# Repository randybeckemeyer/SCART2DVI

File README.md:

# SCART2DVI
SCART to DVI converter ideal for video capture

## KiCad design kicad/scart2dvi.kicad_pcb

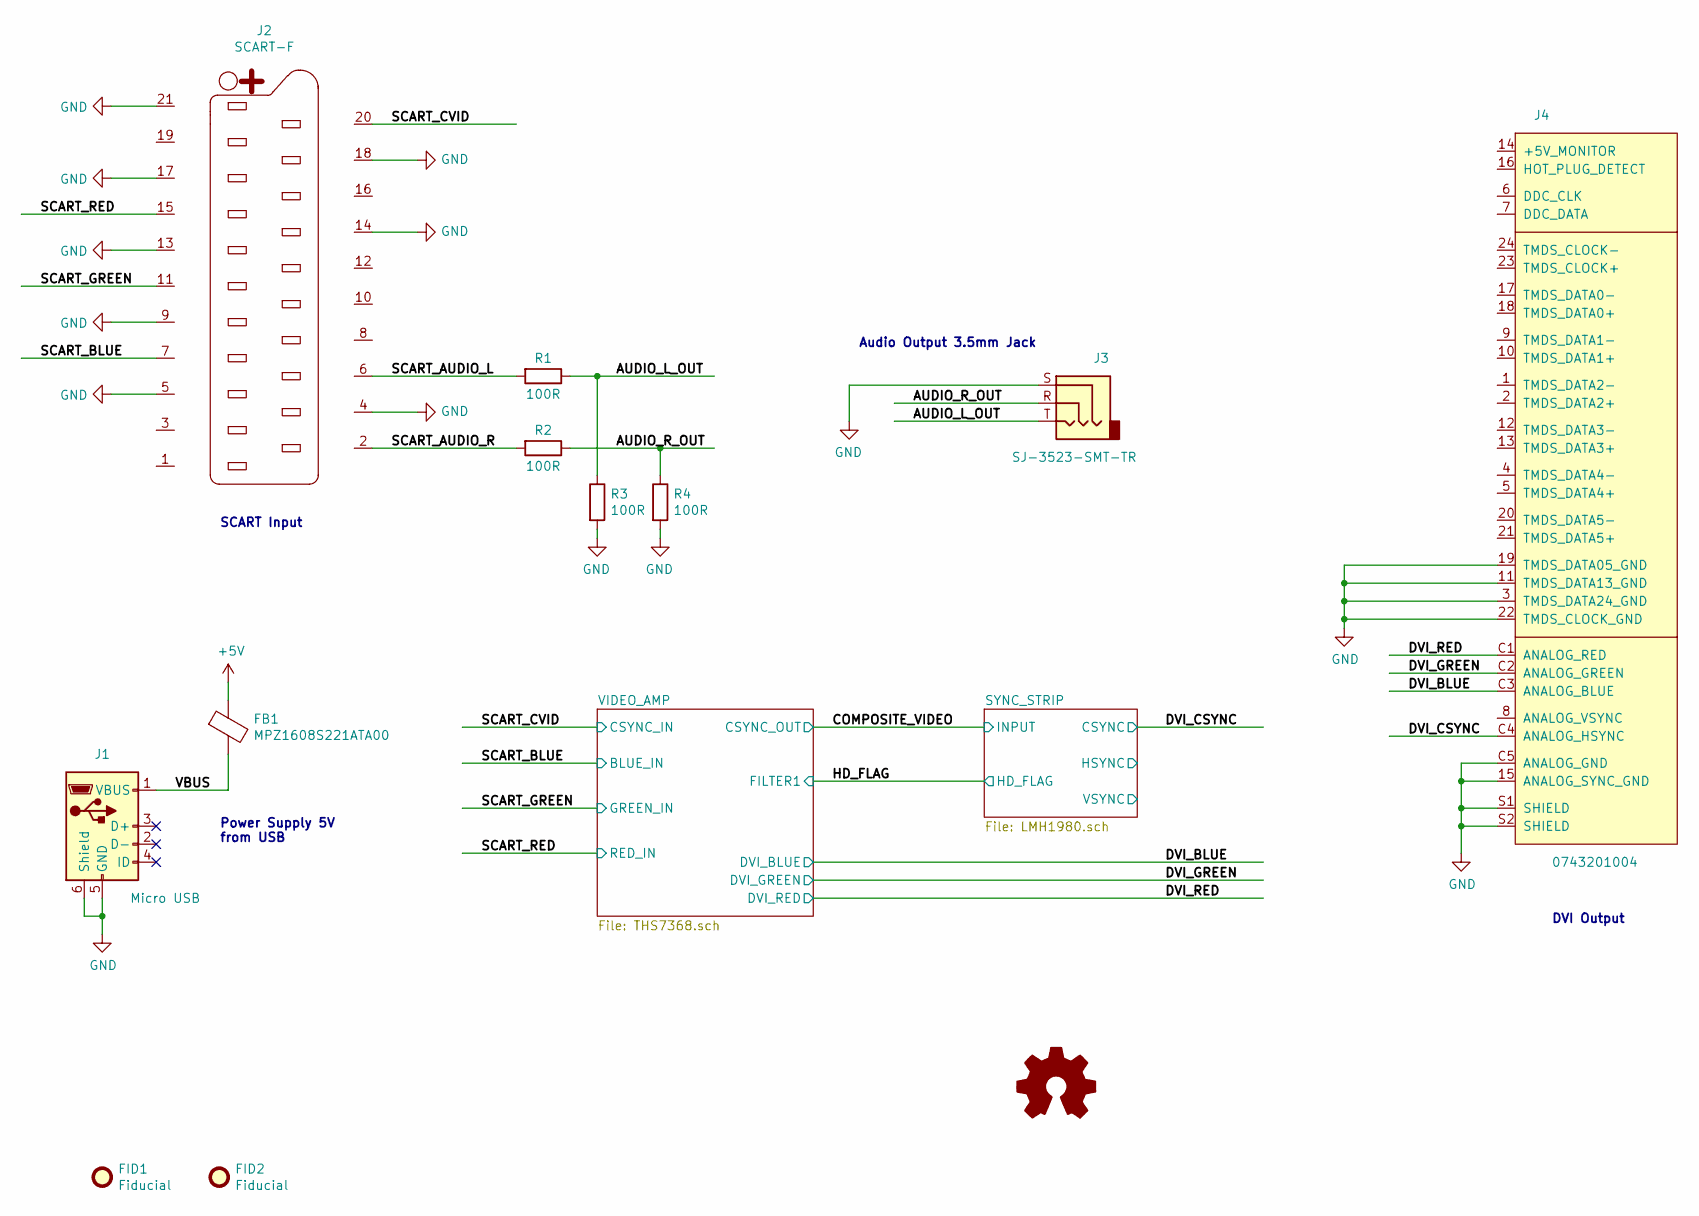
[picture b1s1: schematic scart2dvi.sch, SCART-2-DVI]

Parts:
FB1: MPZ1608S221ATA00; L_0603_1608Metric_Pad1.05x0.95mm_HandSolder; MPN MPZ1608S221ATA00; Digikey 445-1565-1-ND
FID1, FID2: Fiducial; Fiducial_1mm_Mask2mm
J1: Micro USB; USB_Micro-B_Molex-105017-0001; MPN 1050170001; Digikey WM1399CT-ND
J2: SCART-F; SCART-CS-107
J3: SJ-3523-SMT-TR; Jack_3.5mm_CUI_SJ-3523-SMT_Horizontal; MPN SJ-3523-SMT-TR; Digikey CP-3523SJCT-ND
J4: 0743201004; Connector-DVI-0743201004; Digikey WM5600-ND
LOGO1: Logo_Open_Hardware_Small; OSHW-Logo2_14.6x12mm_SilkScreen
R1, R2, R3, R4: 100R; R_0603_1608Metric_Pad1.05x0.95mm_HandSolder; MPN RC0603FR-07100RL; Digikey 311-100HRCT-ND

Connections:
+5V: FB1.1; also elsewhere on the board
/AUDIO_L_OUT: J3.T, R1.1, R3.1
/AUDIO_R_OUT: J3.R, R2.1, R4.1
/DVI_BLUE: J4.C3 (ANALOG_BLUE); also elsewhere on the board
/DVI_CSYNC: J4.C4 (ANALOG_HSYNC); also elsewhere on the board
/DVI_GREEN: J4.C2 (ANALOG_GREEN); also elsewhere on the board
/DVI_RED: J4.C1 (ANALOG_RED); also elsewhere on the board
/SCART_AUDIO_L: J2.6, R1.2
/SCART_AUDIO_R: J2.2, R2.2
/SCART_BLUE: J2.7; also elsewhere on the board
/SCART_CVID: J2.20; also elsewhere on the board
/SCART_GREEN: J2.11; also elsewhere on the board
/SCART_RED: J2.15; also elsewhere on the board
/VBUS: FB1.2, J1.1 (VBUS)
GND: J1.5 (GND), J1.6 (Shield), J2.4, J2.5, J2.9, J2.13, J2.14, J2.17, J2.18, J2.21, J3.S, J4.3 (TMDS_DATA24_GND), J4.11 (TMDS_DATA13_GND), J4.15 (ANALOG_SYNC_GND), J4.19 (TMDS_DATA05_GND), J4.22 (TMDS_CLOCK_GND), J4.C5 (ANALOG_GND), J4.S1 (SHIELD), J4.S2 (SHIELD), R3.2, R4.2; also elsewhere on the board

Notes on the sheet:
Power Supply 5V from USB
Audio Output 3.5mm Jack
DVI Output
SCART Input

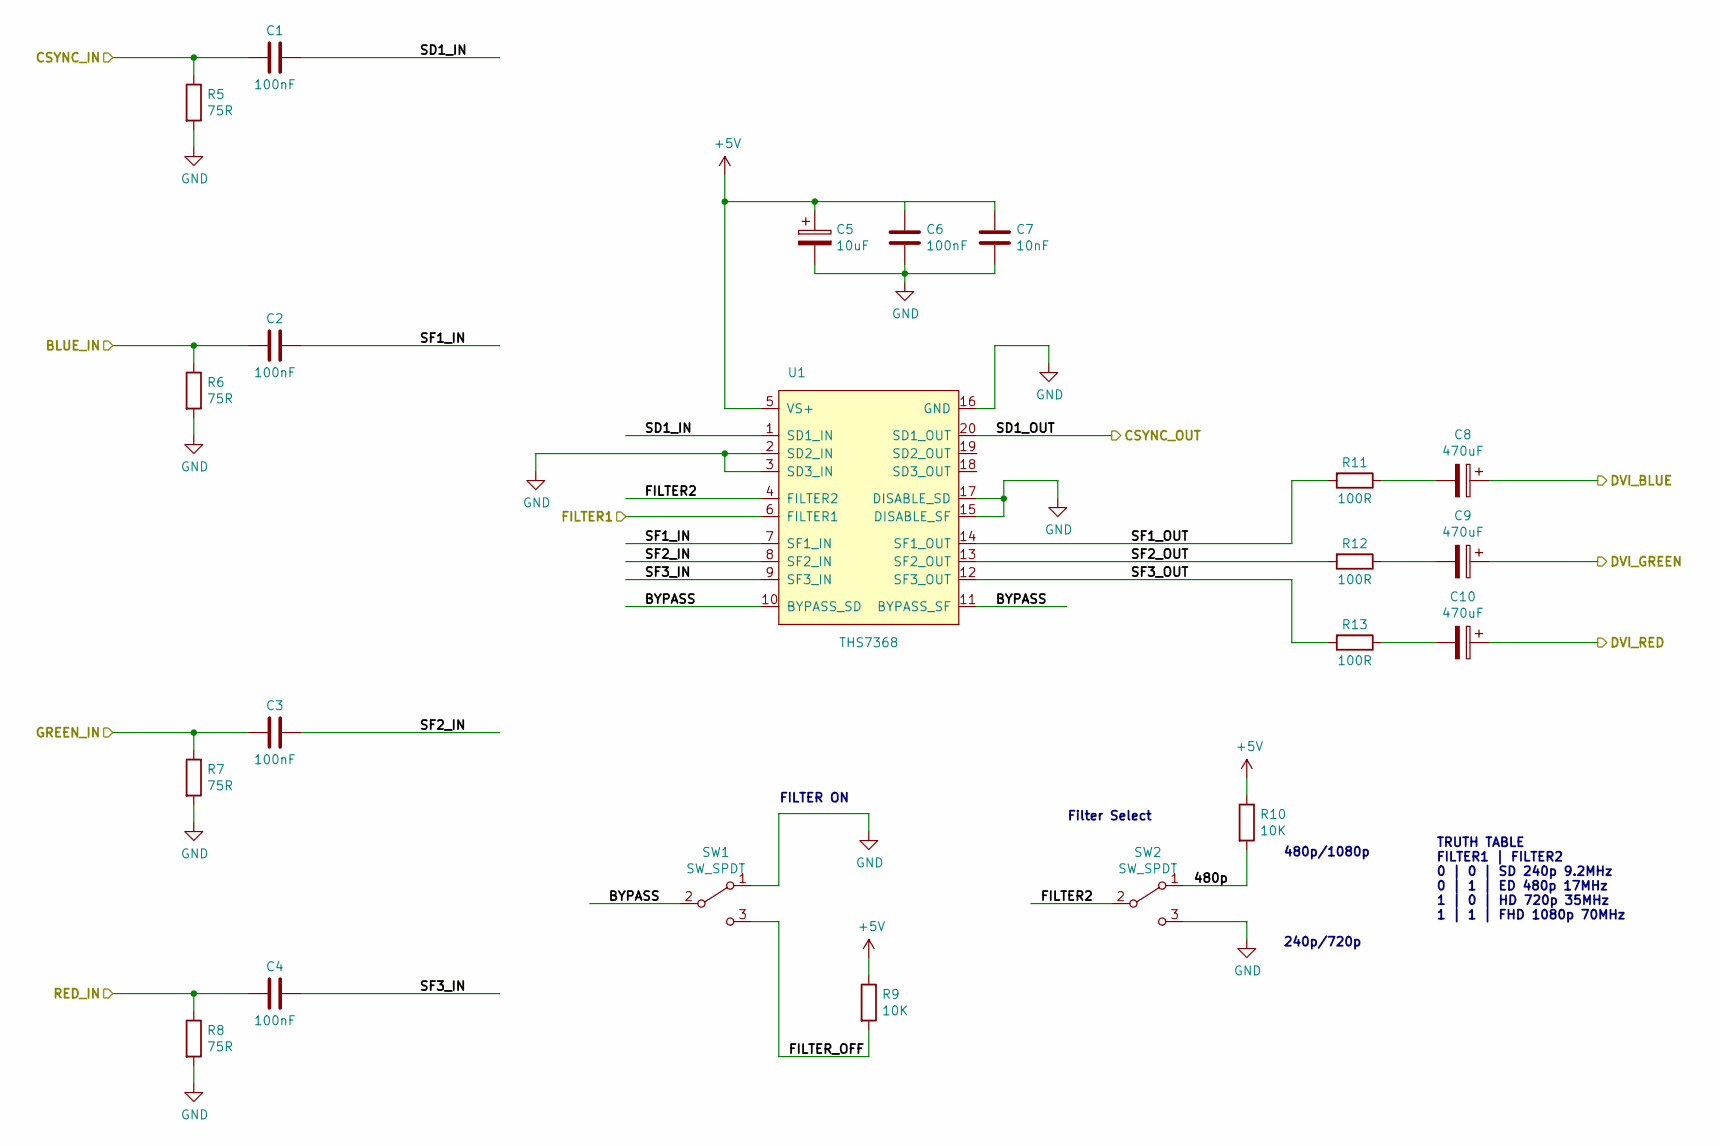
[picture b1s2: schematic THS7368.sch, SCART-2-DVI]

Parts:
C1, C2, C3, C4, C6: 100nF; C_0603_1608Metric_Pad1.05x0.95mm_HandSolder; MPN CC0603KRX7R9BB104; Digikey 311-1344-1-ND
C5: 10uF; CP_EIA-3216-18_Kemet-A_Pad1.58x1.35mm_HandSolder; MPN TAJA106K016RNJ; Digikey 478-1655-1-ND
C7: 10nF; C_0603_1608Metric_Pad1.05x0.95mm_HandSolder; MPN CC0603KRX7R9BB103; Digikey 311-1085-1-ND
C8, C9, C10: 470uF; CP_Elec_8x10.5; MPN EEE-HA1A471UP; Digikey PCE4178CT-ND
R5, R6, R7, R8: 75R; R_0603_1608Metric_Pad1.05x0.95mm_HandSolder; MPN RC0603FR-0775RL; Digikey 311-75.0HRCT-ND
R9, R10: 10K; R_0603_1608Metric_Pad1.05x0.95mm_HandSolder; MPN RC0603FR-0710KL; Digikey 311-10.0KHRCT-ND
R11, R12, R13: 100R; R_0603_1608Metric_Pad1.05x0.95mm_HandSolder; MPN RC0603FR-07100RL; Digikey 311-100HRCT-ND
SW1, SW2: SW_SPDT; SW_NKK_GW12RCV; MPN GW12RCV; Digikey 360-3430-ND
U1: THS7368; TSSOP-20_4.4x6.5mm_P0.65mm; MPN THS7368IPWR; Digikey 296-25625-1-ND

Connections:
+5V: C5.1, C6.1, C7.1, R9.1, R10.1, U1.5 (VS+); also elsewhere on the board
/COMPOSITE_VIDEO: U1.20 (SD1_OUT); also elsewhere on the board
/DVI_BLUE: C8.1; also elsewhere on the board
/DVI_GREEN: C9.1; also elsewhere on the board
/DVI_RED: C10.1; also elsewhere on the board
/HD_FLAG: U1.6 (FILTER1); also elsewhere on the board
/SCART_BLUE: C2.2, R6.1; also elsewhere on the board
/SCART_CVID: C1.2, R5.1; also elsewhere on the board
/SCART_GREEN: C3.2, R7.1; also elsewhere on the board
/SCART_RED: C4.2, R8.1; also elsewhere on the board
/VIDEO_AMP/480p: R10.2, SW2.1 (A)
/VIDEO_AMP/BYPASS: SW1.2 (B), U1.10 (BYPASS_SD), U1.11 (BYPASS_SF)
/VIDEO_AMP/FILTER2: SW2.2 (B), U1.4 (FILTER2)
/VIDEO_AMP/FILTER_OFF: R9.2, SW1.3 (C)
/VIDEO_AMP/SD1_IN: C1.1, U1.1 (SD1_IN)
/VIDEO_AMP/SF1_IN: C2.1, U1.7 (SF1_IN)
/VIDEO_AMP/SF1_OUT: R11.2, U1.14 (SF1_OUT)
/VIDEO_AMP/SF2_IN: C3.1, U1.8 (SF2_IN)
/VIDEO_AMP/SF2_OUT: R12.2, U1.13 (SF2_OUT)
/VIDEO_AMP/SF3_IN: C4.1, U1.9 (SF3_IN)
/VIDEO_AMP/SF3_OUT: R13.2, U1.12 (SF3_OUT)
GND: C5.2, C6.2, C7.2, R5.2, R6.2, R7.2, R8.2, SW1.1 (A), SW2.3 (C), U1.2 (SD2_IN), U1.3 (SD3_IN), U1.15 (DISABLE_SF), U1.16 (GND), U1.17 (DISABLE_SD); also elsewhere on the board
unnamed: C8.2, R11.1
unnamed: C9.2, R12.1
unnamed: C10.2, R13.1

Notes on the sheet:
FILTER ON
TRUTH TABLE FILTER1 | FILTER2 0 | 0 | SD 240p 9.2MHz 0 | 1 | ED 480p 17MHz 1 | 0 | HD 720p 35MHz 1 | 1 | FHD 1080p 70MHz
Filter Select
240p/720p
480p/1080p

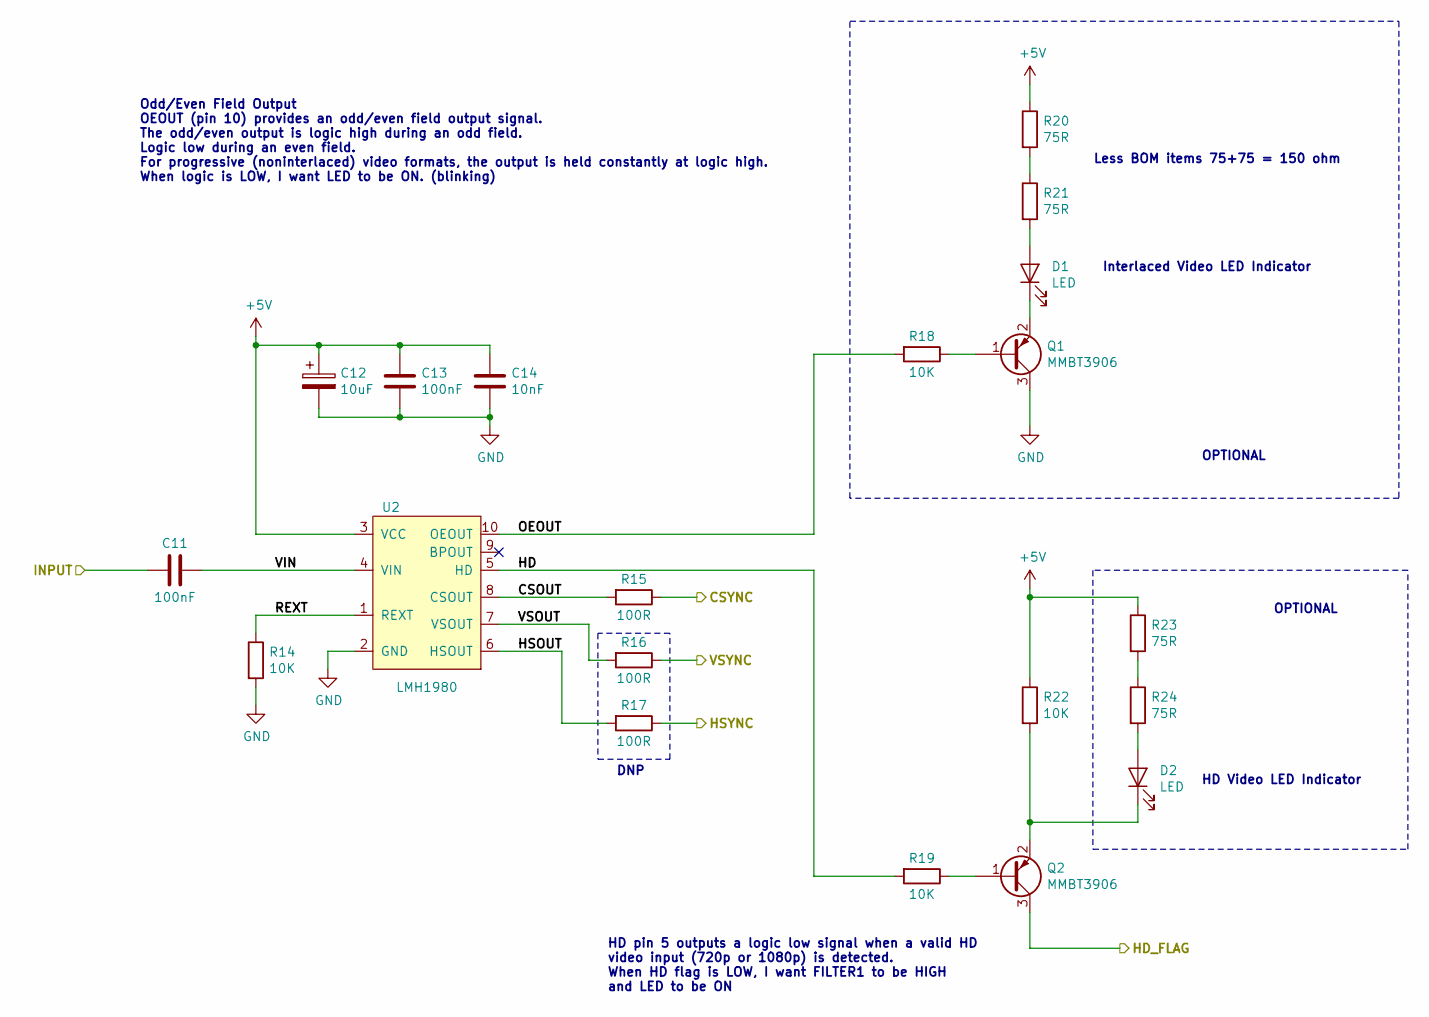
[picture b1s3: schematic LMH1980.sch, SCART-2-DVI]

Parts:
C11, C13: 100nF; C_0603_1608Metric_Pad1.05x0.95mm_HandSolder; MPN CC0603KRX7R9BB104; Digikey 311-1344-1-ND
C12: 10uF; CP_EIA-3216-18_Kemet-A_Pad1.58x1.35mm_HandSolder; MPN TAJA106K016RNJ; Digikey 478-1655-1-ND
C14: 10nF; C_0603_1608Metric_Pad1.05x0.95mm_HandSolder; MPN CC0603KRX7R9BB103; Digikey 311-1085-1-ND
D1, D2: LED; LED_0603_1608Metric_Pad1.05x0.95mm_HandSolder; MPN LTST-C190GKT; Digikey 160-1183-1-ND
Q1, Q2: MMBT3906; SOT-23; MPN MMBT3906LT1G; Digikey MMBT3906LT1GOSCT-ND
R14, R18, R19, R22: 10K; R_0603_1608Metric_Pad1.05x0.95mm_HandSolder; MPN RC0603FR-0710KL; Digikey 311-10.0KHRCT-ND
R15, R16, R17: 100R; R_0603_1608Metric_Pad1.05x0.95mm_HandSolder; MPN RC0603FR-07100RL; Digikey 311-100HRCT-ND
R20, R21, R23, R24: 75R; R_0603_1608Metric_Pad1.05x0.95mm_HandSolder; MPN RC0603FR-0775RL; Digikey 311-75.0HRCT-ND
U2: LMH1980; TSSOP-10_3x3mm_P0.5mm; MPN LMH1980MM/NOPB; Digikey LMH1980MM/NOPBCT-ND

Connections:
+5V: C12.1, C13.1, C14.1, R20.1, R22.1, R23.1, U2.3 (VCC); also elsewhere on the board
/COMPOSITE_VIDEO: C11.2; also elsewhere on the board
/DVI_CSYNC: R15.1; also elsewhere on the board
/HD_FLAG: Q2.3 (C); also elsewhere on the board
/SYNC_STRIP/CSOUT: R15.2, U2.8 (CSOUT)
/SYNC_STRIP/HD: R19.2, U2.5 (HD)
/SYNC_STRIP/HSOUT: R17.2, U2.6 (HSOUT)
/SYNC_STRIP/HSYNC: R17.1
/SYNC_STRIP/OEOUT: R18.2, U2.10 (OEOUT)
/SYNC_STRIP/REXT: R14.1, U2.1 (REXT)
/SYNC_STRIP/VIN: C11.1, U2.4 (VIN)
/SYNC_STRIP/VSOUT: R16.2, U2.7 (VSOUT)
/SYNC_STRIP/VSYNC: R16.1
GND: C12.2, C13.2, C14.2, Q1.3 (C), R14.2, U2.2 (GND); also elsewhere on the board
unnamed: D1.1 (K), Q1.2 (E)
unnamed: D1.2 (A), R21.2
unnamed: D2.1 (K), Q2.2 (E), R22.2
unnamed: D2.2 (A), R24.2
unnamed: Q1.1 (B), R18.1
unnamed: Q2.1 (B), R19.1
unnamed: R20.2, R21.1
unnamed: R23.2, R24.1

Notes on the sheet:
HD pin 5 outputs a logic low signal when a valid HD video input (720p or 1080p) is detected. When HD flag is LOW, I want FILTER1 to be HIGH and LED to be ON
Odd/Even Field Output OEOUT (pin 10) provides an odd/even field output signal. The odd/even output is logic high during an odd field. Logic low during an even field. For progressive (noninterlaced) video formats, the output is held constantly at logic high. When logic is LOW, I want LED to be ON. (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
Interlaced Video LED Indicator
HD Video LED Indicator
Less BOM items 75+75 = 150 ohm
DNP
OPTIONAL

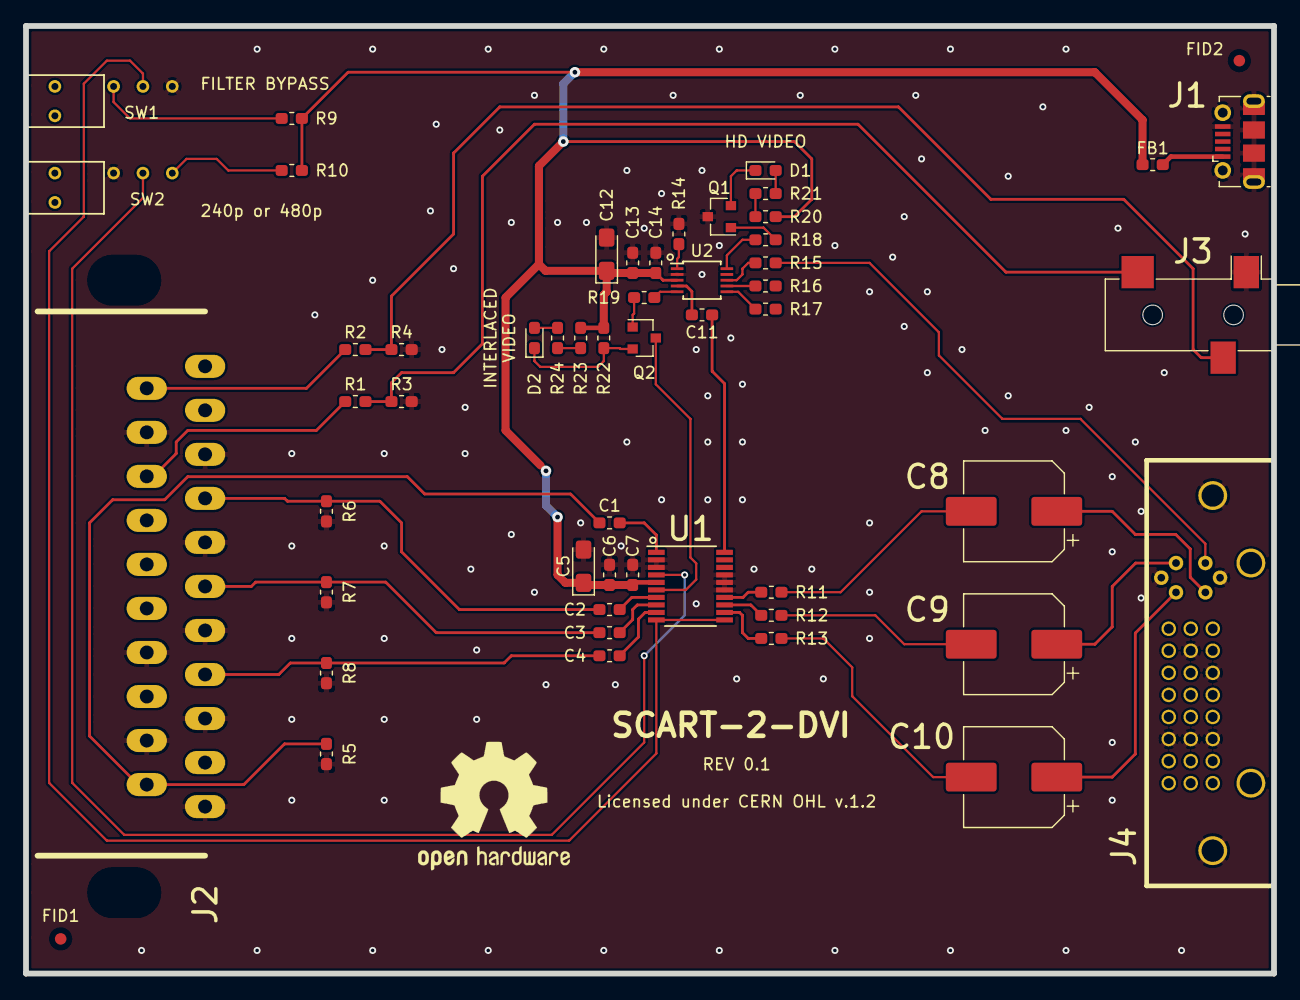
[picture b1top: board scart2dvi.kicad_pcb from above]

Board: 2 copper layers, 108.0 x 82.0 mm, 54 parts (0 on the bottom side), 46 nets.

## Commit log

2019-03-24 moved all files to a kicad folder
2019-03-24 pull down disable pins

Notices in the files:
kicad/scart2dvi.kicad_pcb:
Licensed under CERN OHL v.1.2
